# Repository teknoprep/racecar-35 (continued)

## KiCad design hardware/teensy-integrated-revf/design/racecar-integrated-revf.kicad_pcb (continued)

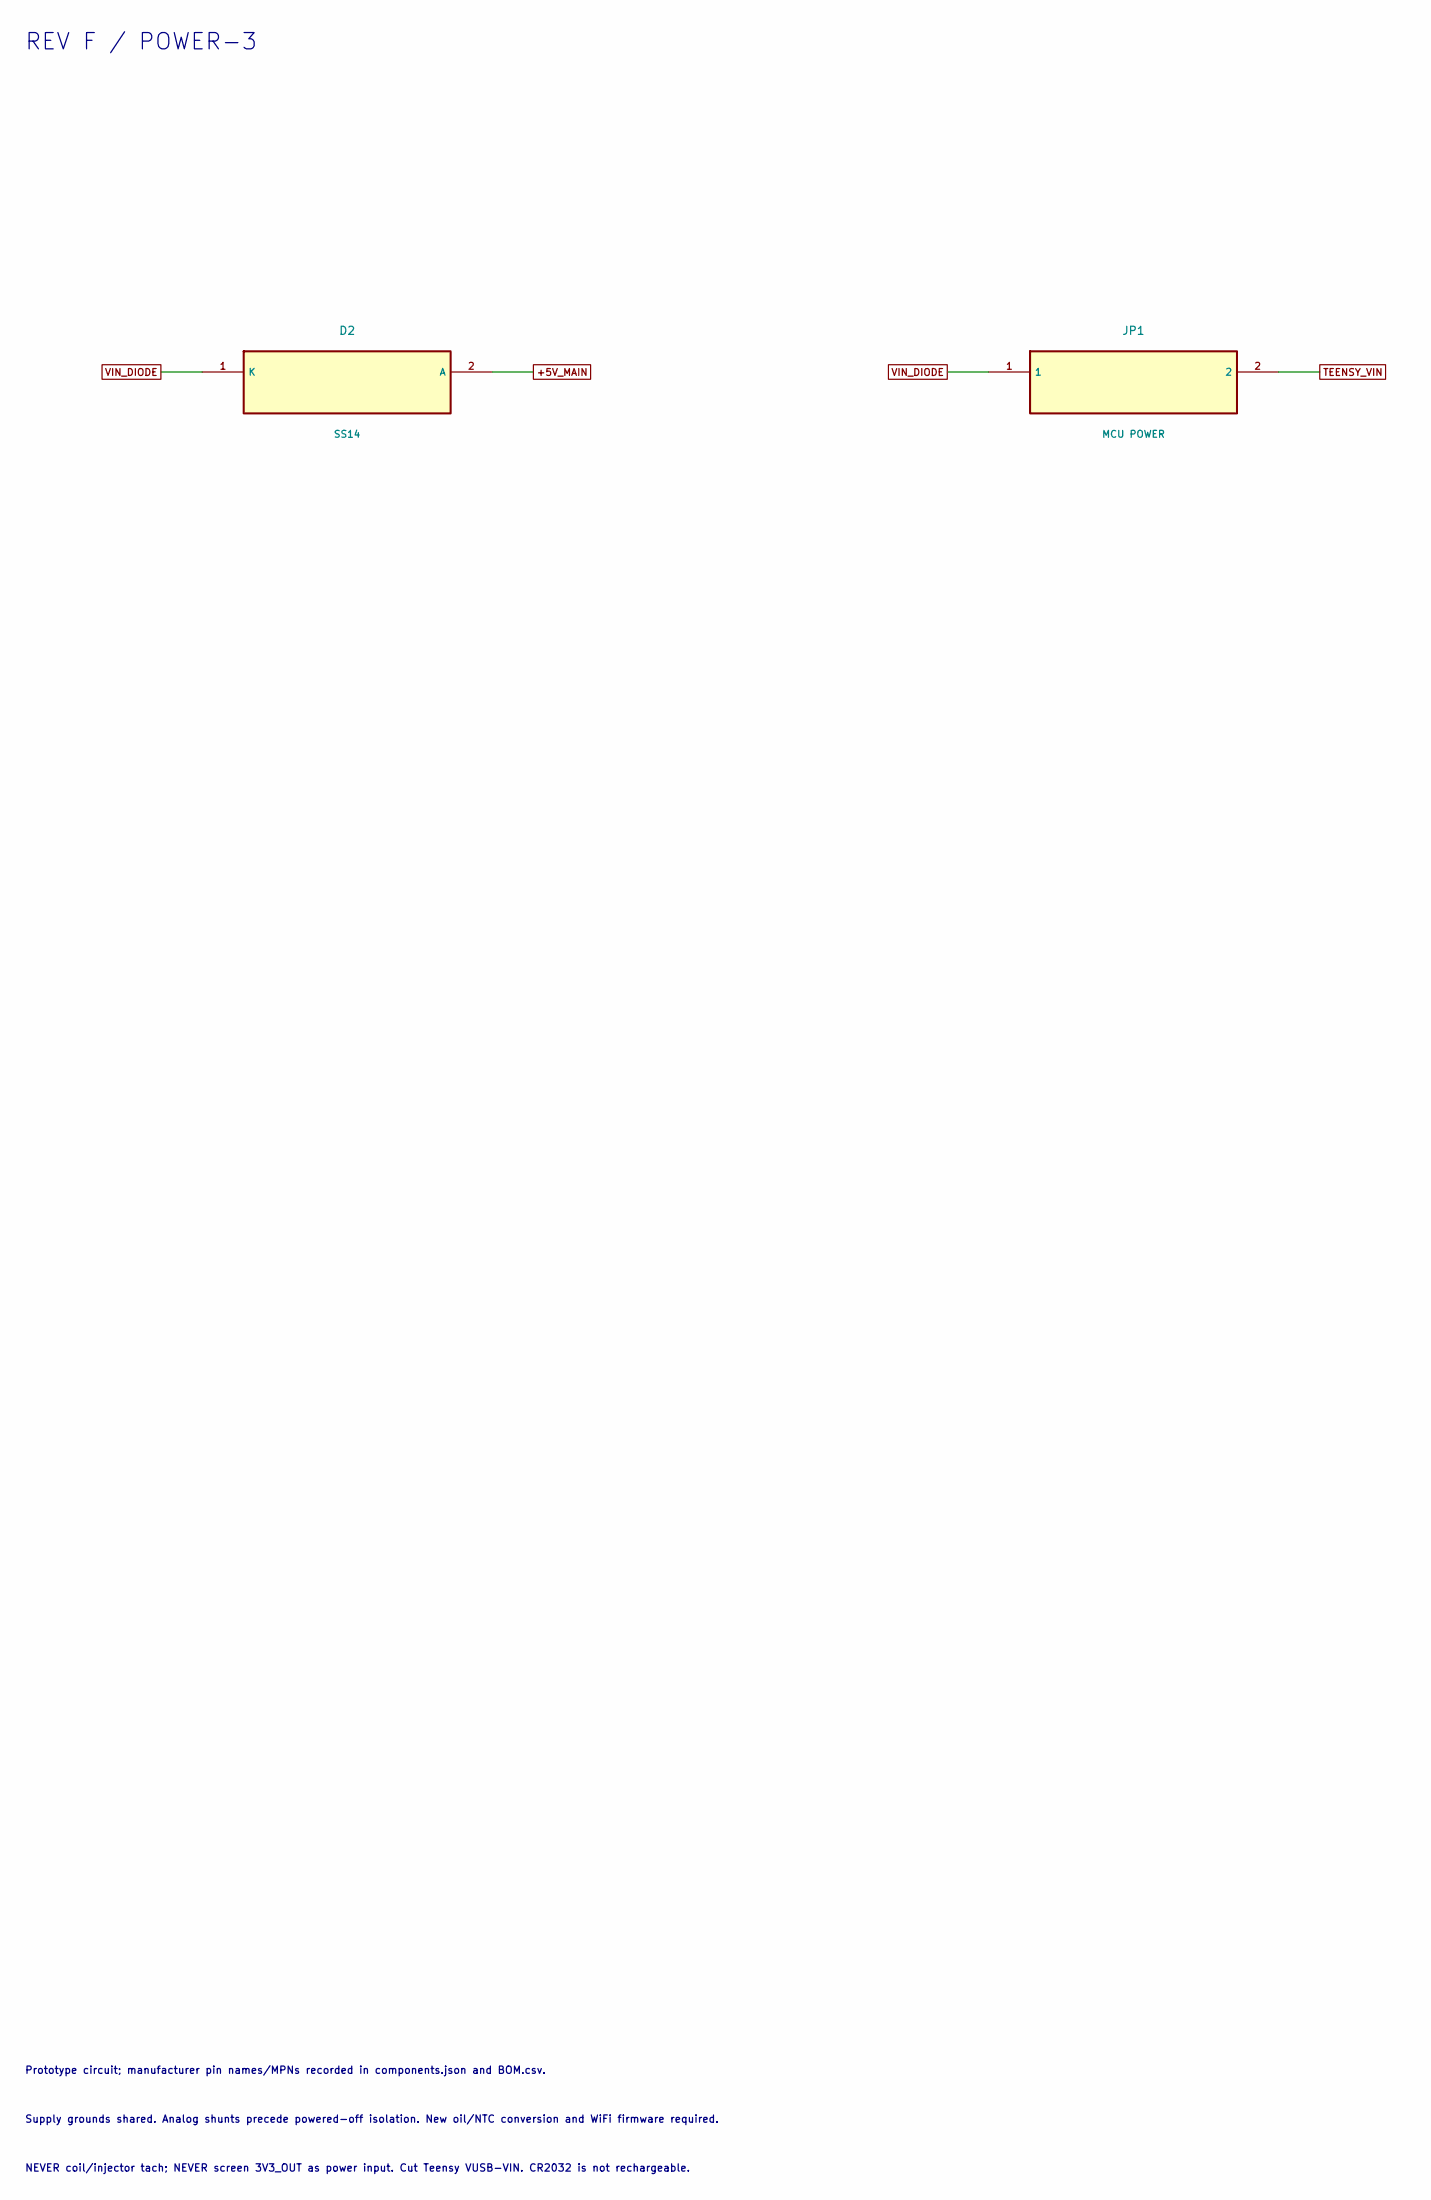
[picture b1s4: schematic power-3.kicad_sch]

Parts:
D2: SS14; D_SMA
JP1: MCU POWER; PinHeader_1x02_P2.54mm_Vertical

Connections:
+5V_MAIN: D2.2 (A); also elsewhere on the board
TEENSY_VIN: JP1.2; also elsewhere on the board
VIN_DIODE: D2.1 (K), JP1.1

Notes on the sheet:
REV F / POWER-3
Prototype circuit; manufacturer pin names/MPNs recorded in components.json and BOM.csv.
Supply grounds shared. Analog shunts precede powered-off isolation. New oil/NTC conversion and WiFi firmware required.
NEVER coil/injector tach; NEVER screen 3V3_OUT as power input. Cut Teensy VUSB-VIN. CR2032 is not rechargeable.

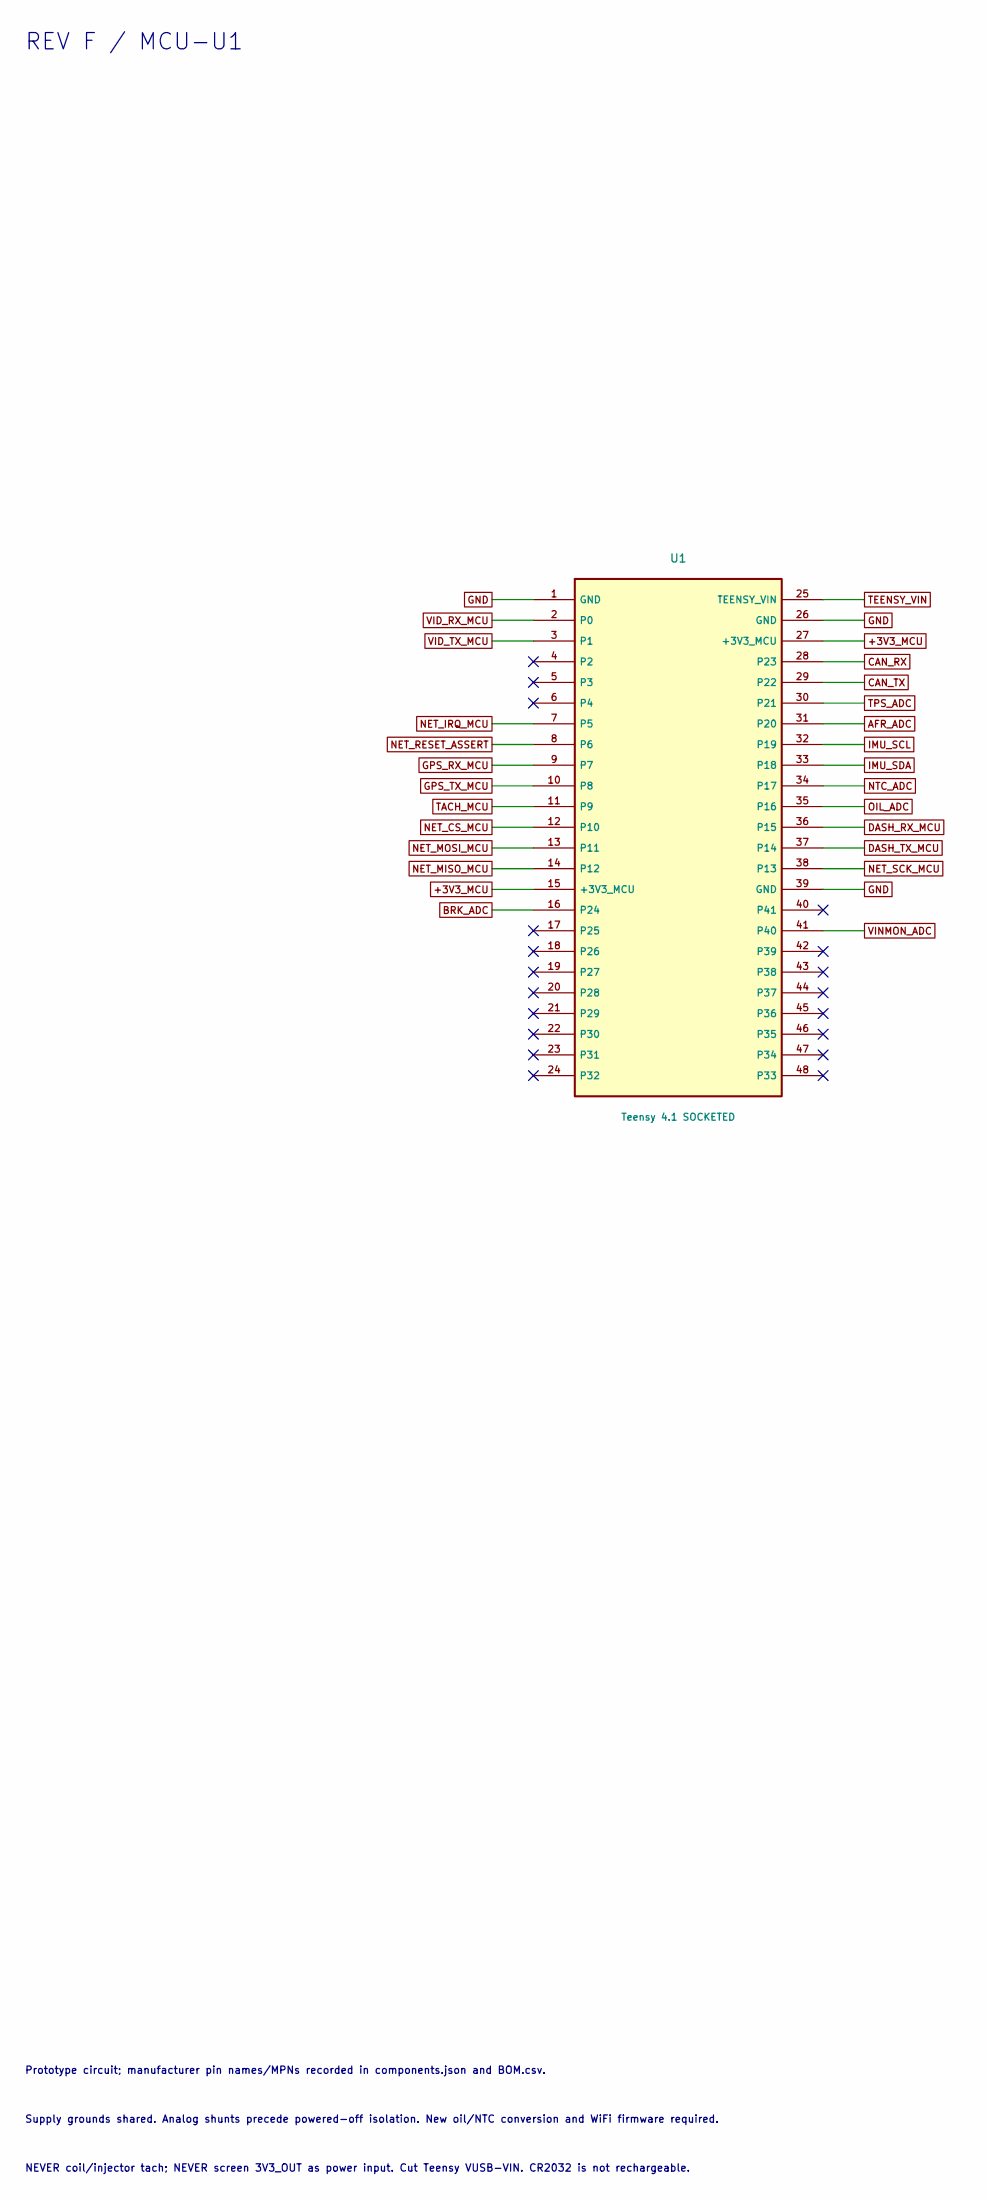
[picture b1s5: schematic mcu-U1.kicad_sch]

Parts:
U1: Teensy 4.1 SOCKETED; Teensy41_Socket

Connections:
+3V3_MCU: U1.15 (+3V3_MCU), U1.27 (+3V3_MCU); also elsewhere on the board
AFR_ADC: U1.31 (P20); also elsewhere on the board
BRK_ADC: U1.16 (P24); also elsewhere on the board
CAN_RX: U1.28 (P23); also elsewhere on the board
CAN_TX: U1.29 (P22); also elsewhere on the board
DASH_RX_MCU: U1.36 (P15); also elsewhere on the board
DASH_TX_MCU: U1.37 (P14); also elsewhere on the board
GND: U1.1 (GND), U1.26 (GND), U1.39 (GND); also elsewhere on the board
GPS_RX_MCU: U1.9 (P7); also elsewhere on the board
GPS_TX_MCU: U1.10 (P8); also elsewhere on the board
IMU_SCL: U1.32 (P19); also elsewhere on the board
IMU_SDA: U1.33 (P18); also elsewhere on the board
NET_CS_MCU: U1.12 (P10); also elsewhere on the board
NET_IRQ_MCU: U1.7 (P5); also elsewhere on the board
NET_MISO_MCU: U1.14 (P12); also elsewhere on the board
NET_MOSI_MCU: U1.13 (P11); also elsewhere on the board
NET_RESET_ASSERT: U1.8 (P6); also elsewhere on the board
NET_SCK_MCU: U1.38 (P13); also elsewhere on the board
NTC_ADC: U1.34 (P17); also elsewhere on the board
OIL_ADC: U1.35 (P16); also elsewhere on the board
TACH_MCU: U1.11 (P9); also elsewhere on the board
TEENSY_VIN: U1.25 (TEENSY_VIN); also elsewhere on the board
TPS_ADC: U1.30 (P21); also elsewhere on the board
VID_RX_MCU: U1.2 (P0); also elsewhere on the board
VID_TX_MCU: U1.3 (P1); also elsewhere on the board
VINMON_ADC: U1.41 (P40); also elsewhere on the board

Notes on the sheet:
REV F / MCU-U1
Prototype circuit; manufacturer pin names/MPNs recorded in components.json and BOM.csv.
Supply grounds shared. Analog shunts precede powered-off isolation. New oil/NTC conversion and WiFi firmware required.
NEVER coil/injector tach; NEVER screen 3V3_OUT as power input. Cut Teensy VUSB-VIN. CR2032 is not rechargeable.

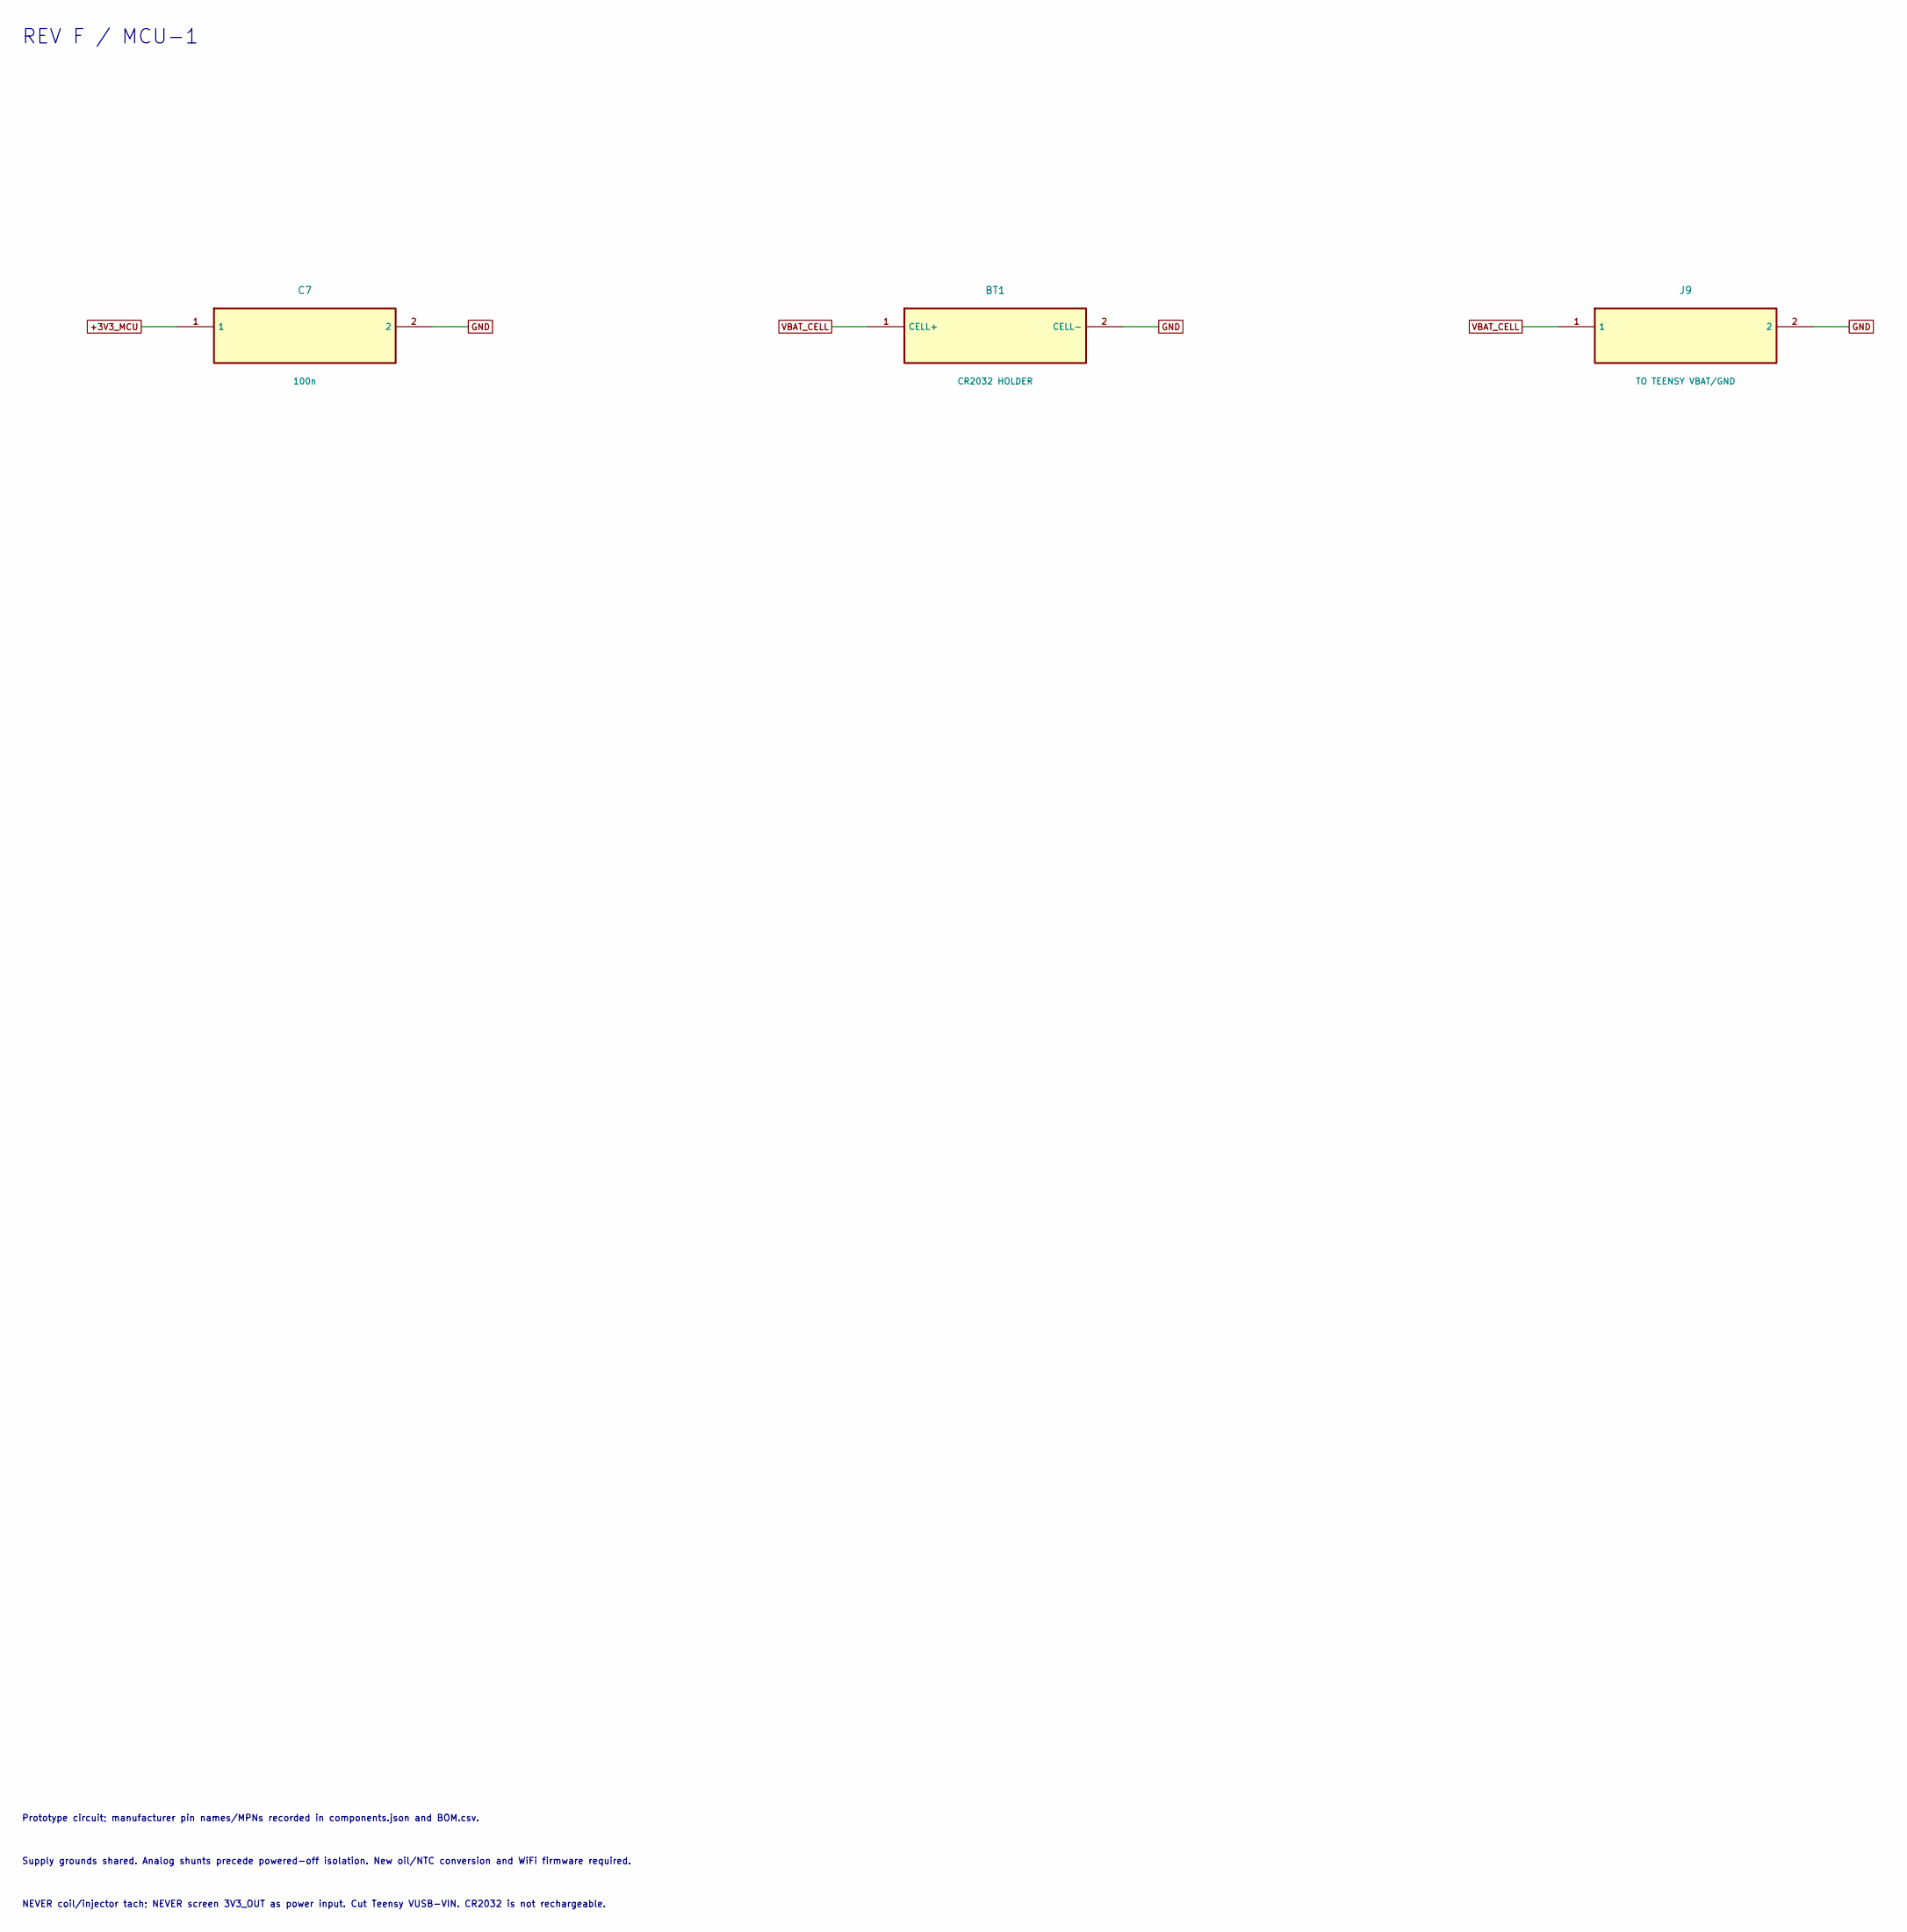
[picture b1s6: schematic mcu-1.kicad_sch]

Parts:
BT1: CR2032 HOLDER; BatteryHolder_Keystone_1058_1x2032
C7: 100n; C_0805_2012Metric
J9: TO TEENSY VBAT/GND; JST_XH_B2B-XH-A_1x02_P2.50mm_Vertical

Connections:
+3V3_MCU: C7.1; also elsewhere on the board
GND: BT1.2 (CELL-), C7.2, J9.2; also elsewhere on the board
VBAT_CELL: BT1.1 (CELL+), J9.1

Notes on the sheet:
REV F / MCU-1
Prototype circuit; manufacturer pin names/MPNs recorded in components.json and BOM.csv.
Supply grounds shared. Analog shunts precede powered-off isolation. New oil/NTC conversion and WiFi firmware required.
NEVER coil/injector tach; NEVER screen 3V3_OUT as power input. Cut Teensy VUSB-VIN. CR2032 is not rechargeable.

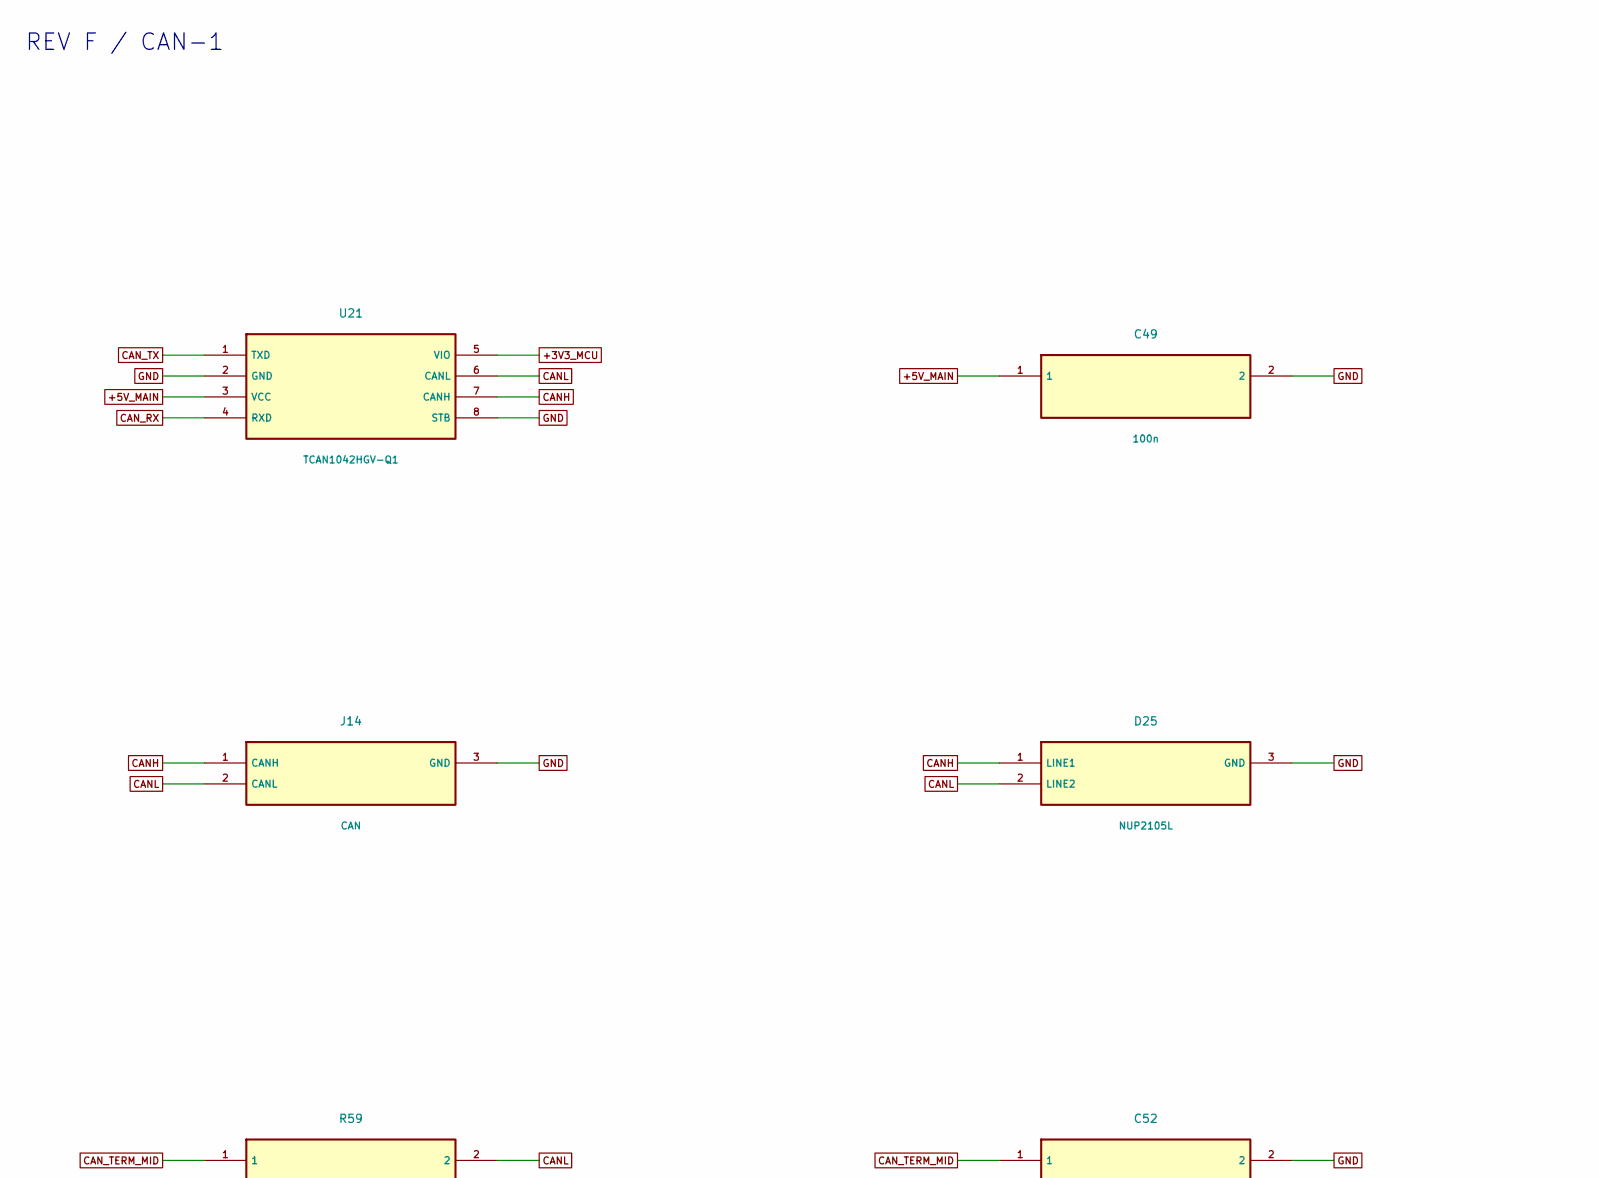
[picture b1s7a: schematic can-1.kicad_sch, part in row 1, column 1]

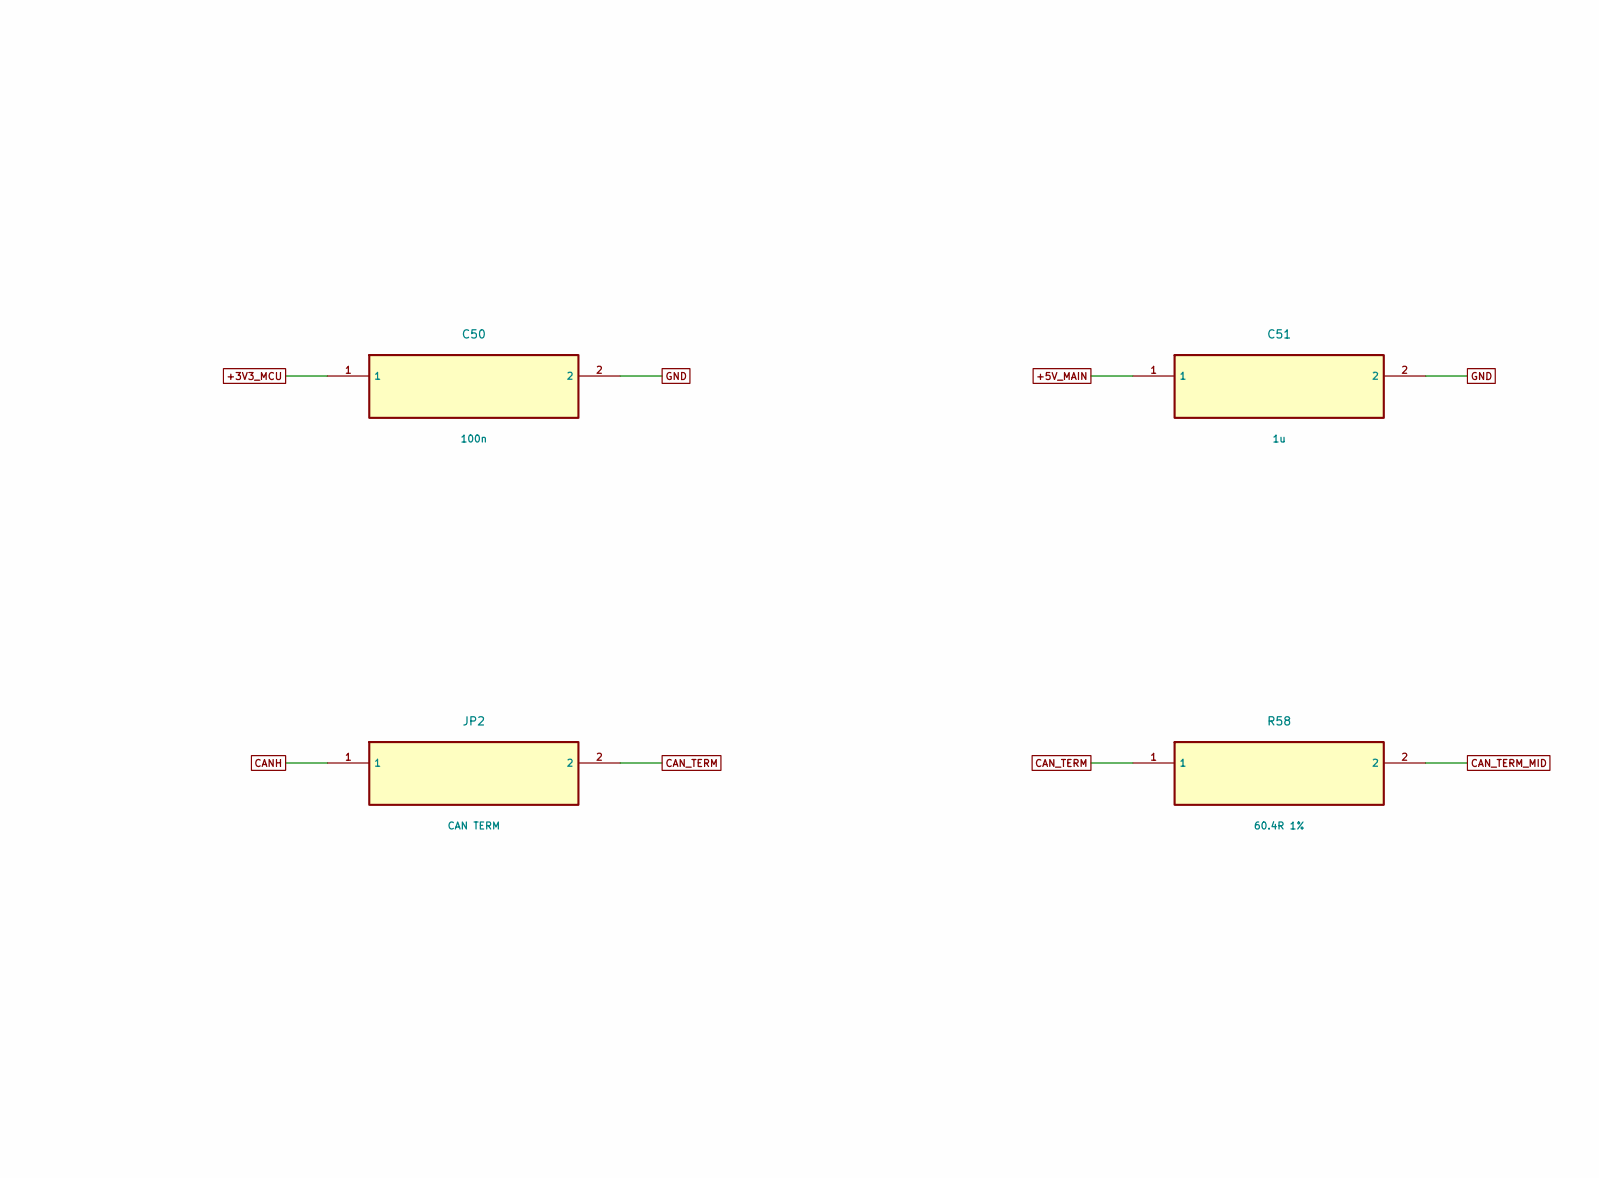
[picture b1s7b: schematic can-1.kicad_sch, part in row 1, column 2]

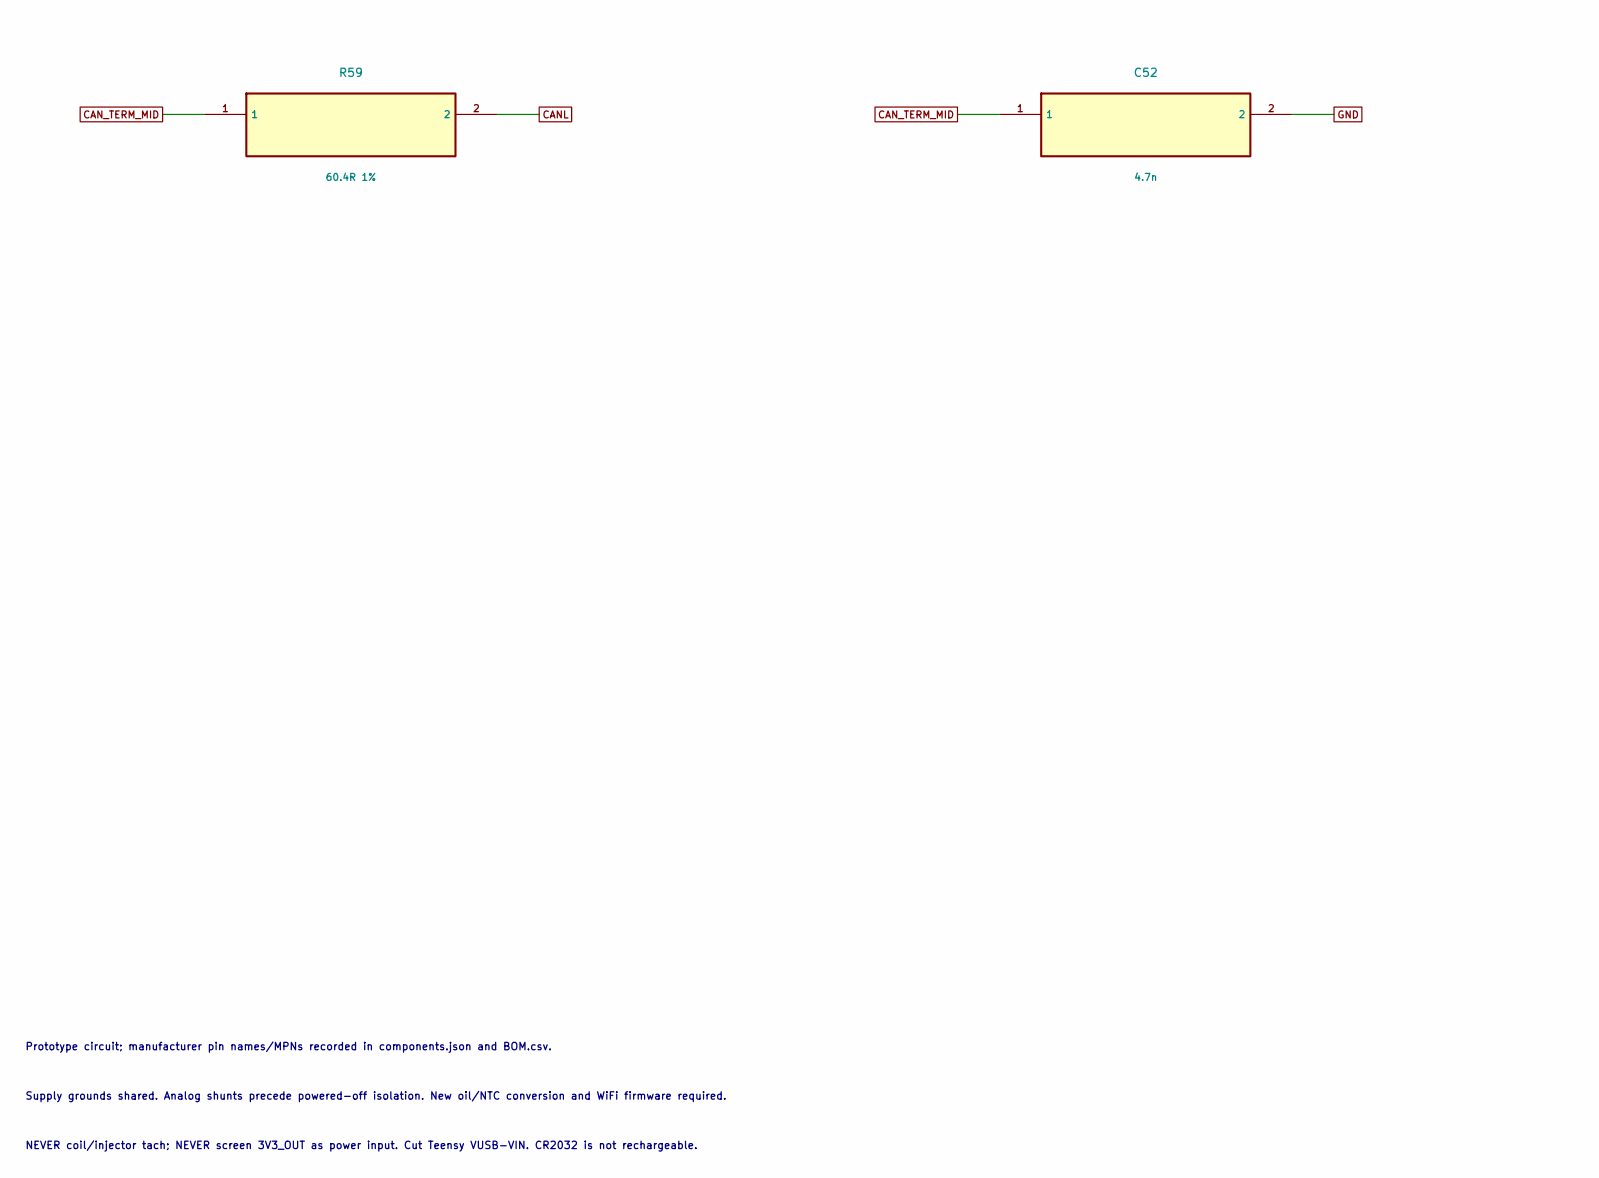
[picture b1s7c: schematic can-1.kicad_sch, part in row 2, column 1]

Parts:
C49, C50: 100n; C_0805_2012Metric
C51: 1u; C_0805_2012Metric
C52: 4.7n; C_0805_2012Metric
D25: NUP2105L; SOT-23
J14: CAN; TerminalBlock_Phoenix_MKDS-1,5-3-5.08_1x03_P5.08mm_Horizont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
JP2: CAN TERM; PinHeader_1x02_P2.54mm_Vertical
R58, R59: 60.4R 1%; R_0805_2012Metric
U21: TCAN1042HGV-Q1; SOIC-8_3.9x4.9mm_P1.27mm

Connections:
+3V3_MCU: C50.1, U21.5 (VIO); also elsewhere on the board
+5V_MAIN: C49.1, C51.1, U21.3 (VCC); also elsewhere on the board
CANH: D25.1 (LINE1), J14.1 (CANH), JP2.1, U21.7 (CANH)
CANL: D25.2 (LINE2), J14.2 (CANL), R59.2, U21.6 (CANL)
CAN_RX: U21.4 (RXD); also elsewhere on the board
CAN_TERM: JP2.2, R58.1
CAN_TERM_MID: C52.1, R58.2, R59.1
CAN_TX: U21.1 (TXD); also elsewhere on the board
GND: C49.2, C50.2, C51.2, C52.2, D25.3 (GND), J14.3 (GND), U21.2 (GND), U21.8 (STB); also elsewhere on the board

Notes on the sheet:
REV F / CAN-1
Prototype circuit; manufacturer pin names/MPNs recorded in components.json and BOM.csv.
Supply grounds shared. Analog shunts precede powered-off isolation. New oil/NTC conversion and WiFi firmware required.
NEVER coil/injector tach; NEVER screen 3V3_OUT as power input. Cut Teensy VUSB-VIN. CR2032 is not rechargeable.
